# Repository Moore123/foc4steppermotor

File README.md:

### foc4steppermotor

The target of this project is to create a board for developing protocol of FOC steppermotor controler

### Passed:
```
    1.extern board power feed
    2.MCU running
    3.MCU flash
```

### Tobe test:
```
    1.FOC driven steppermotor
    2.rs485 
    3.A13333 SPI feed back
```

### MayBe FIX
```
    SWIO  <- pull-up
    SWCLK <- pull-dn
```

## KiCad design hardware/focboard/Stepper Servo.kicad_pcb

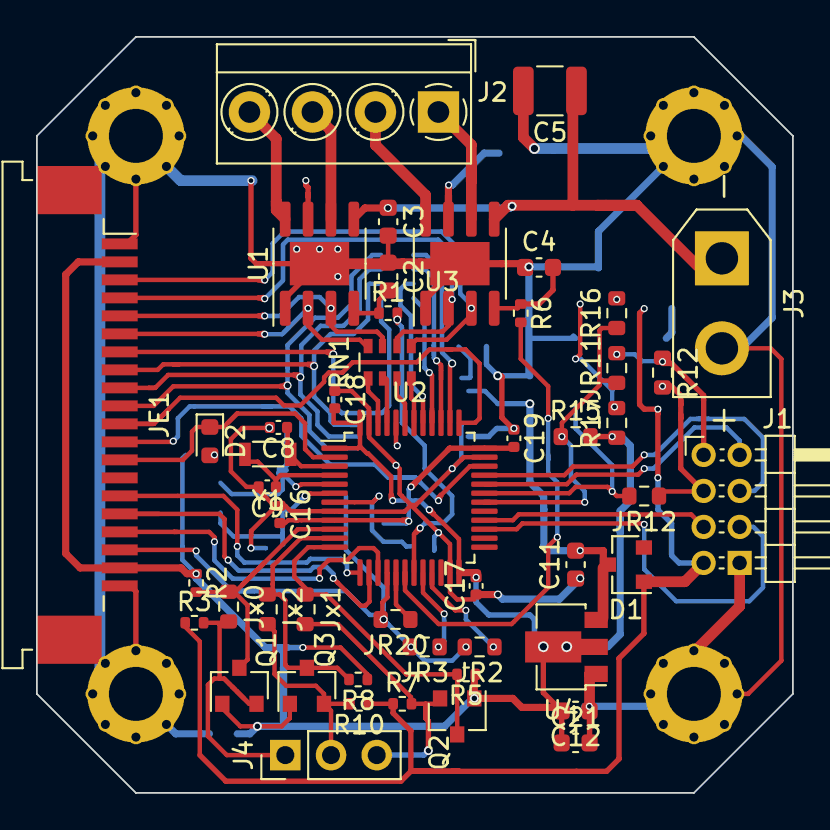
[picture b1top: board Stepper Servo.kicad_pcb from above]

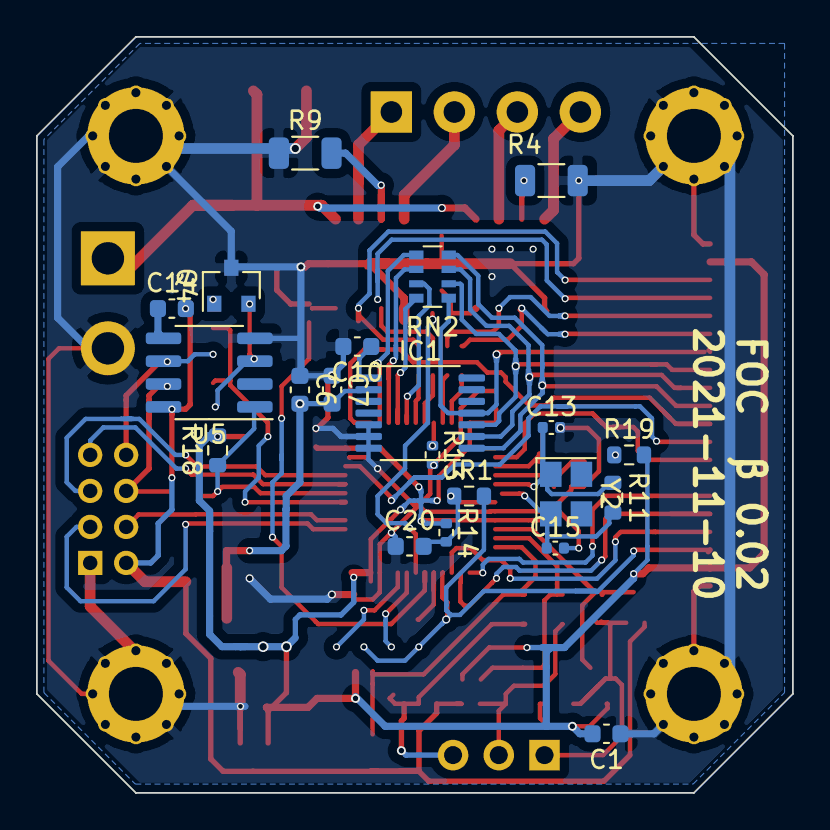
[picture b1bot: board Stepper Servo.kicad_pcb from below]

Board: 2 copper layers, 42.0 x 42.0 mm, 74 parts (21 on the bottom side), 66 nets.

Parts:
C1, C2, C3, C4, C6, C7, C10, C20, C21: 100nF; C_0603_1608Metric
C5: 100uF; C_1210_3225Metric
C8, C9: 10pF; C_0402_1005Metric
C11: 10uF; C_0603_1608Metric
C12: 22uf; C_0603_1608Metric
C13, C15: 22pF; C_0402_1005Metric
C14: 0.1uF; C_0603_1608Metric
C16, C17, C18, C19: 100nF; C_0402_1005Metric
D1: BAT64-05; SOT-23
D2: LED; LED_0603_1608Metric
H1, H2, H3, H4: MountingHole_Pad; MountingHole_3.2mm_M3_Pad_Via
IC1: A1333LLETR-5-T; TSSOP-14_4.4x5mm_P0.65mm
J1: Inputs; PinHeader_2x04_P2.00mm_Horizontal
J2: Motor; TerminalBlock_MetzConnect_Type059_RT06304HBWC_1x04_P3.50mm_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
J3: Conn_01x02_MountingPin; AMASS_XT30UPB-F_1x02_P5.0mm_Vertical
J4: Conn_01x03_Female; PinHeader_1x03_P2.54mm_Vertical
JE1: Conn_01x20; TE_2-84953-0_1x20-1MP_P1.0mm_Horizontal
JR1, JR2, JR3, JR20: 0R; R_0603_1608Metric
JR11, JR12: 0; R_0603_1608Metric
Jx0, Jx1, Jx2: 0; R_0603_1608Metric
Q1, Q2, Q3: FDN337N; SOT-23
Q4: Q_NPN_BCE; SOT-23
R1, R6: 1K; R_0402_1005Metric
R2, R3, R5, R7, R8, R10, R13, R14: 10K; R_0402_1005Metric
R4, R9: 0.1; R_1206_3216Metric
R11: 1M; R_0603_1608Metric
R12: 120R; R_0603_1608Metric
R15, R17, R18: 10K; R_0603_1608Metric
R16: 1K; R_0603_1608Metric
R19: 1k; R_0603_1608Metric
RN1: 100; R_Array_Convex_4x0603
RN2: 10; R_Array_Convex_4x0603
U1, U3: A4950E; SOIC-8-1EP_3.9x4.9mm_P1.27mm_EP2.41x3.3mm
U2: STM32F030CCTx; LQFP-48_7x7mm_P0.5mm
U4: AMS1117-3.3; SOT-89-3
U5: MAX485E; SOP-8_3.76x4.96mm_P1.27mm
Y1: 32K768; FC-135_32768kHz Crystal
Y2: 8MHz; Crystal_SMD_3225-4Pin_3.2x2.5mm

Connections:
1A: J2.2, U3.8
1B: J2.1, U3.6
2A: J2.4, U1.8
2B: J2.3, U1.6
+3V3: C1.2, C12.2, C16.2, C17.2, C18.2, C19.2, C21.1, JE1.2, JE1.19, Q1.1, Q2.1, Q3.1, R2.1, R5.1, R8.1, R14.1, R15.2, R17.1, R18.2, R19.2, U2.1, U2.9, U2.24, U2.36, U2.48, U4.2
+5V: C6.2, C7.2, C11.2, D1.3, IC1.2, U4.3
A2: RN2.5, U2.38
A2_1: IC1.8, JE1.10, RN2.4
A9450_IN1: RN1.4, U2.42
A9450_IN2: RN1.3, U2.43
A9450_IN3: RN1.2, U2.45
A9450_IN4: RN1.1, U2.46
BOOT0: R13.1, U2.44
BackEnable: J1.4, U2.33
DIR: J4.2, Jx2.2, Q3.2, R10.2
DIR1: Jx2.1, Q3.3, R8.2, U2.11
E13: JE1.15, U2.13
E14: JE1.16, U2.14
E15: JE1.17, U2.15
EJ16: JE1.18, JR1.2, JR2.2, JR3.2, JR20.2, U2.16
EJ17: JR20.1, U2.17
EJ20: JR3.1, U2.20
EJ21: JR2.1, U2.21
EN: J4.3, Jx1.2, Q2.2, R7.2
EN1: Jx1.1, Q2.3, R5.2, U2.12
FrontEnable: J1.2, U2.32
GND: C1.1, C2.1, C3.2, C4.1, C5.2, C6.1, C7.1, C8.2, C9.2, C10.2, C11.1, C12.1, C13.2, C15.2, C16.1, C17.1, C18.1, C19.1, C20.1, C21.2, H1.1, H2.1, H3.1, H4.1, IC1.5, IC1.6, IC1.7, J1.8, J3.2, JE1.1, JE1.20, Q4.3, R4.1, R9.1, R13.2, U1.1, U1.9, U2.8, U2.23, U2.35, U2.47, U3.1, U3.9, U4.1, U5.4
IN1: JE1.3, RN1.5, U3.3
IN2: JE1.4, RN1.6, U3.2
IN3: JE1.5, RN1.7, U1.3
IN4: JE1.6, RN1.8, U1.2
LeftEnable: J1.5, U2.28
MAX485A: J1.1, JR11.2, R12.1, U5.6
MAX485B: J1.3, JR12.1, R12.2, U5.7
MISO: RN2.8, U2.40
MISO1: IC1.11, JE1.7, RN2.1
MOSI: RN2.7, U2.41
MOSI1: IC1.10, JE1.8, RN2.2
NRST: C20.2, JR1.1, R14.2, U2.7
unnamed: C2.2, R1.1, U1.4
unnamed: C4.2, R6.1, U3.4
unnamed: C10.1, IC1.1
unnamed: C14.1, U5.5
unnamed: D2.2, R19.1
unnamed: Q4.1, R16.2
unnamed: Q4.2, R17.2, U5.3
unnamed: R4.2, U1.7
unnamed: R9.2, U3.7
OSC32IN: C8.1, U2.3, Y1.1
OSC32OUT: C9.1, U2.4, Y1.2
RightEnable: J1.6, U2.27
SCK: RN2.6, U2.39
SCK1: IC1.9, JE1.9, RN2.3
STP: J4.1, Jx0.2, Q1.2, R3.2
STP1: Jx0.1, Q1.3, R2.2, U2.10
SWCLK: JE1.11, U2.37
SWDIO: JE1.12, U2.34
USART1_RX: JR12.2, R18.1, U2.31, U5.1
USART1_TX: JR11.1, R15.1, R16.1, U2.30
VCC: C14.2, D1.1, J1.7, R3.1, R7.1, R10.1, U5.8
VMOT: C3.1, C5.1, J3.1, U1.5, U3.5
VREF12: R6.2, U2.18
VREF34: R1.2, U2.19
XTALin: C13.1, R11.1, U2.5, Y2.1
XTALout: C15.1, R11.2, U2.6, Y2.2
bLED: D2.1, JE1.13, U2.2

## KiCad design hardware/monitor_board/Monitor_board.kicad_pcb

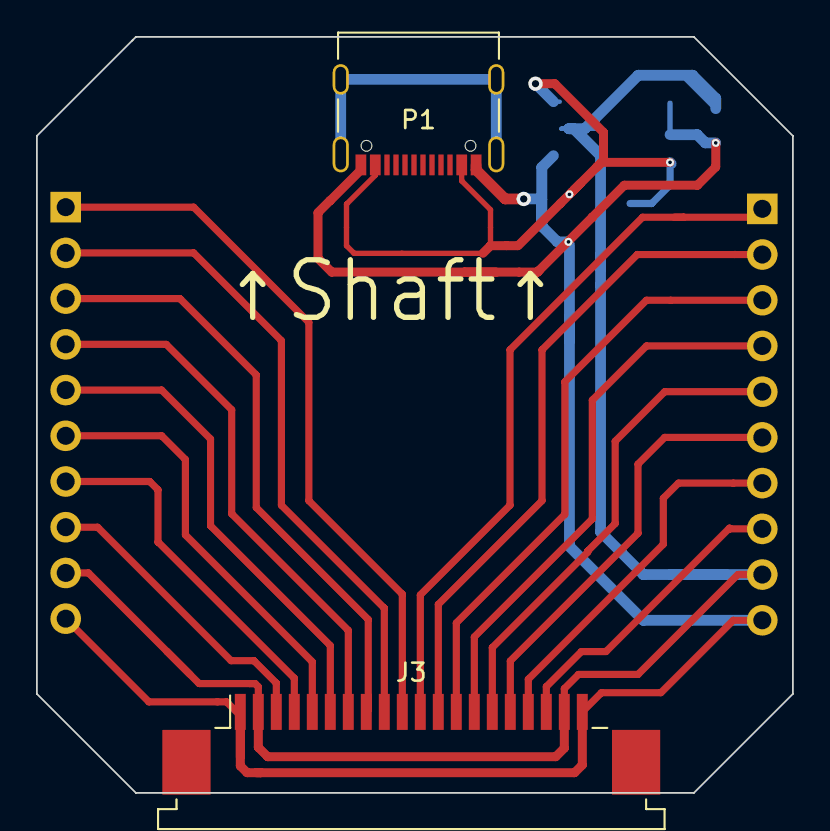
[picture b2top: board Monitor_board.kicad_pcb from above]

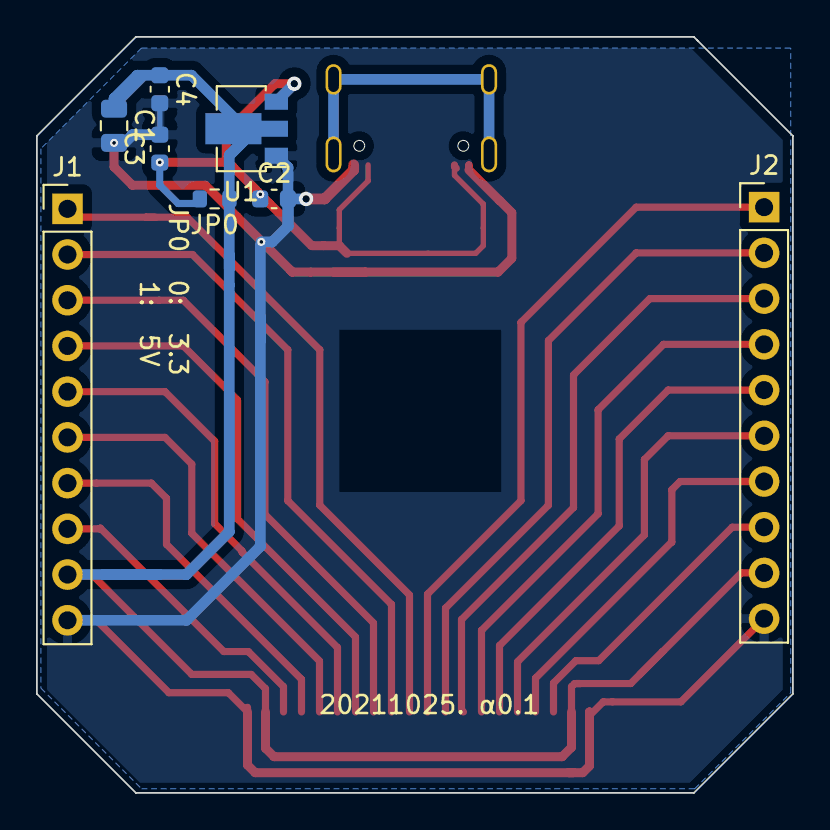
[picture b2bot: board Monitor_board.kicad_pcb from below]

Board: 2 copper layers, 42.0 x 42.0 mm, 10 parts (8 on the bottom side), 19 nets.

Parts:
C1: 22uF; C_0805_2012Metric
C2: C; C_0603_1608Metric
C3, C4: 0.1uF; C_0603_1608Metric
J1, J2: Conn_01x10_Female; PinHeader_1x10_P2.54mm_Vertical
J3: Conn_01x20_MountingPin; TE_2-84953-0_1x20-1MP_P1.0mm_Horizontal
JP0: 0; R_0603_1608Metric
P1: USB_C_Plug; USB_C_Receptacle_Palconn_UTC16-G
U1: AP1117-33; SOT-89-3

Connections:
GND: C1.2, C2.2, C3.2, C4.2, J1.10, J2.10, J3.1, J3.20, P1.A1, P1.A12, P1.B1, P1.B12, U1.1
unnamed: C1.1, C4.1, J1.9, J2.9, J3.2, J3.19, JP0.1, U1.2
unnamed: C2.1, C3.1, JP0.2, P1.A4, P1.A9, P1.B4, P1.B9, U1.3
unnamed: J1.1, J3.11
unnamed: J1.2, J3.12
unnamed: J1.3, J3.13
unnamed: J1.4, J3.14
unnamed: J1.5, J3.15
unnamed: J1.6, J3.16
unnamed: J1.7, J3.17
unnamed: J1.8, J3.18
unnamed: J2.1, J3.10
unnamed: J2.2, J3.9
unnamed: J2.3, J3.8
unnamed: J2.4, J3.7
unnamed: J2.5, J3.6
unnamed: J2.6, J3.5
unnamed: J2.7, J3.4
unnamed: J2.8, J3.3

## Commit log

2021-11-27 add bare-metal firmware for enssential testing board
2021-11-27 append extern board schema
2021-11-30 Todo list conform
2021-11-30 README.md confirm
2021-12-01 typo & foc4 board
2021-12-02 useful datasheets
2021-12-02 README.md fix
